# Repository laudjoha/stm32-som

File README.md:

# stm32-som
An application ready, hand solderable, stm32 system on module.

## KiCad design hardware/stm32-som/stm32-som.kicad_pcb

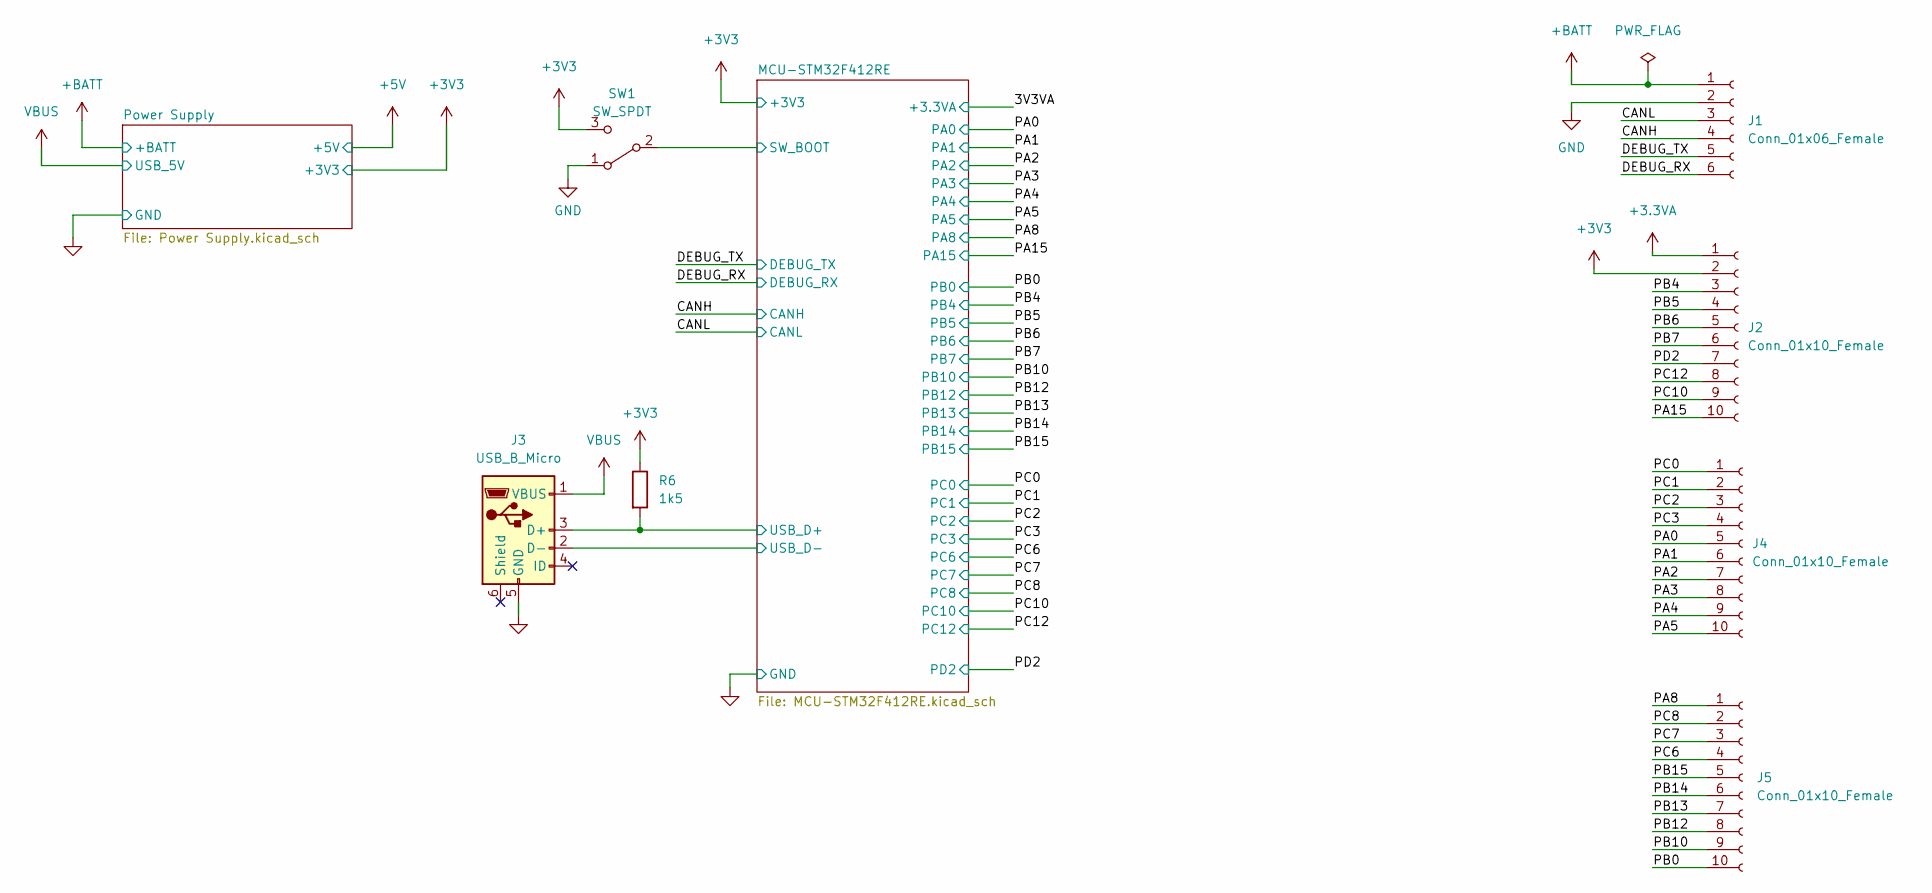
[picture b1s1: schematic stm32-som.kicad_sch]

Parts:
J1: Conn_01x06_Female; 1x6p-2.54mm-castellated
J2, J4, J5: Conn_01x10_Female; 1x10p-2.54mm-castellated
J3: USB_B_Micro; USB_Micro-B_Amphenol_10118194_Horizontal; JLC C132563
R6: 1k5; R_0402_1005Metric
SW1: SW_SPDT; SW_SPDT_PCM12

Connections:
+3.3VA: J2.1; also elsewhere on the board
+3V3: J2.2, R6.1, SW1.3 (C); also elsewhere on the board
+BATT: J1.1; also elsewhere on the board
/CANH: J1.4; also elsewhere on the board
/CANL: J1.3; also elsewhere on the board
/DEBUG_RX: J1.6; also elsewhere on the board
/DEBUG_TX: J1.5; also elsewhere on the board
/MCU-STM32F412RE/SW_BOOT: SW1.2 (B); also elsewhere on the board
/MCU-STM32F412RE/USB_D+: J3.3 (D+), R6.2; also elsewhere on the board
/MCU-STM32F412RE/USB_D-: J3.2 (D-); also elsewhere on the board
/PA0: J4.5; also elsewhere on the board
/PA1: J4.6; also elsewhere on the board
/PA2: J4.7; also elsewhere on the board
/PA3: J4.8; also elsewhere on the board
/PA4: J4.9; also elsewhere on the board
/PA5: J4.10; also elsewhere on the board
/PA8: J5.1; also elsewhere on the board
/PA15: J2.10; also elsewhere on the board
/PB0: J5.10; also elsewhere on the board
/PB4: J2.3; also elsewhere on the board
/PB5: J2.4; also elsewhere on the board
/PB6: J2.5; also elsewhere on the board
/PB7: J2.6; also elsewhere on the board
/PB10: J5.9; also elsewhere on the board
/PB12: J5.8; also elsewhere on the board
/PB13: J5.7; also elsewhere on the board
/PB14: J5.6; also elsewhere on the board
/PB15: J5.5; also elsewhere on the board
/PC0: J4.1; also elsewhere on the board
/PC1: J4.2; also elsewhere on the board
/PC2: J4.3; also elsewhere on the board
/PC3: J4.4; also elsewhere on the board
/PC6: J5.4; also elsewhere on the board
/PC7: J5.3; also elsewhere on the board
/PC8: J5.2; also elsewhere on the board
/PC10: J2.9; also elsewhere on the board
/PC12: J2.8; also elsewhere on the board
/PD2: J2.7; also elsewhere on the board
GND: J1.2, J3.5 (GND), SW1.1 (A); also elsewhere on the board
VBUS: J3.1 (VBUS); also elsewhere on the board

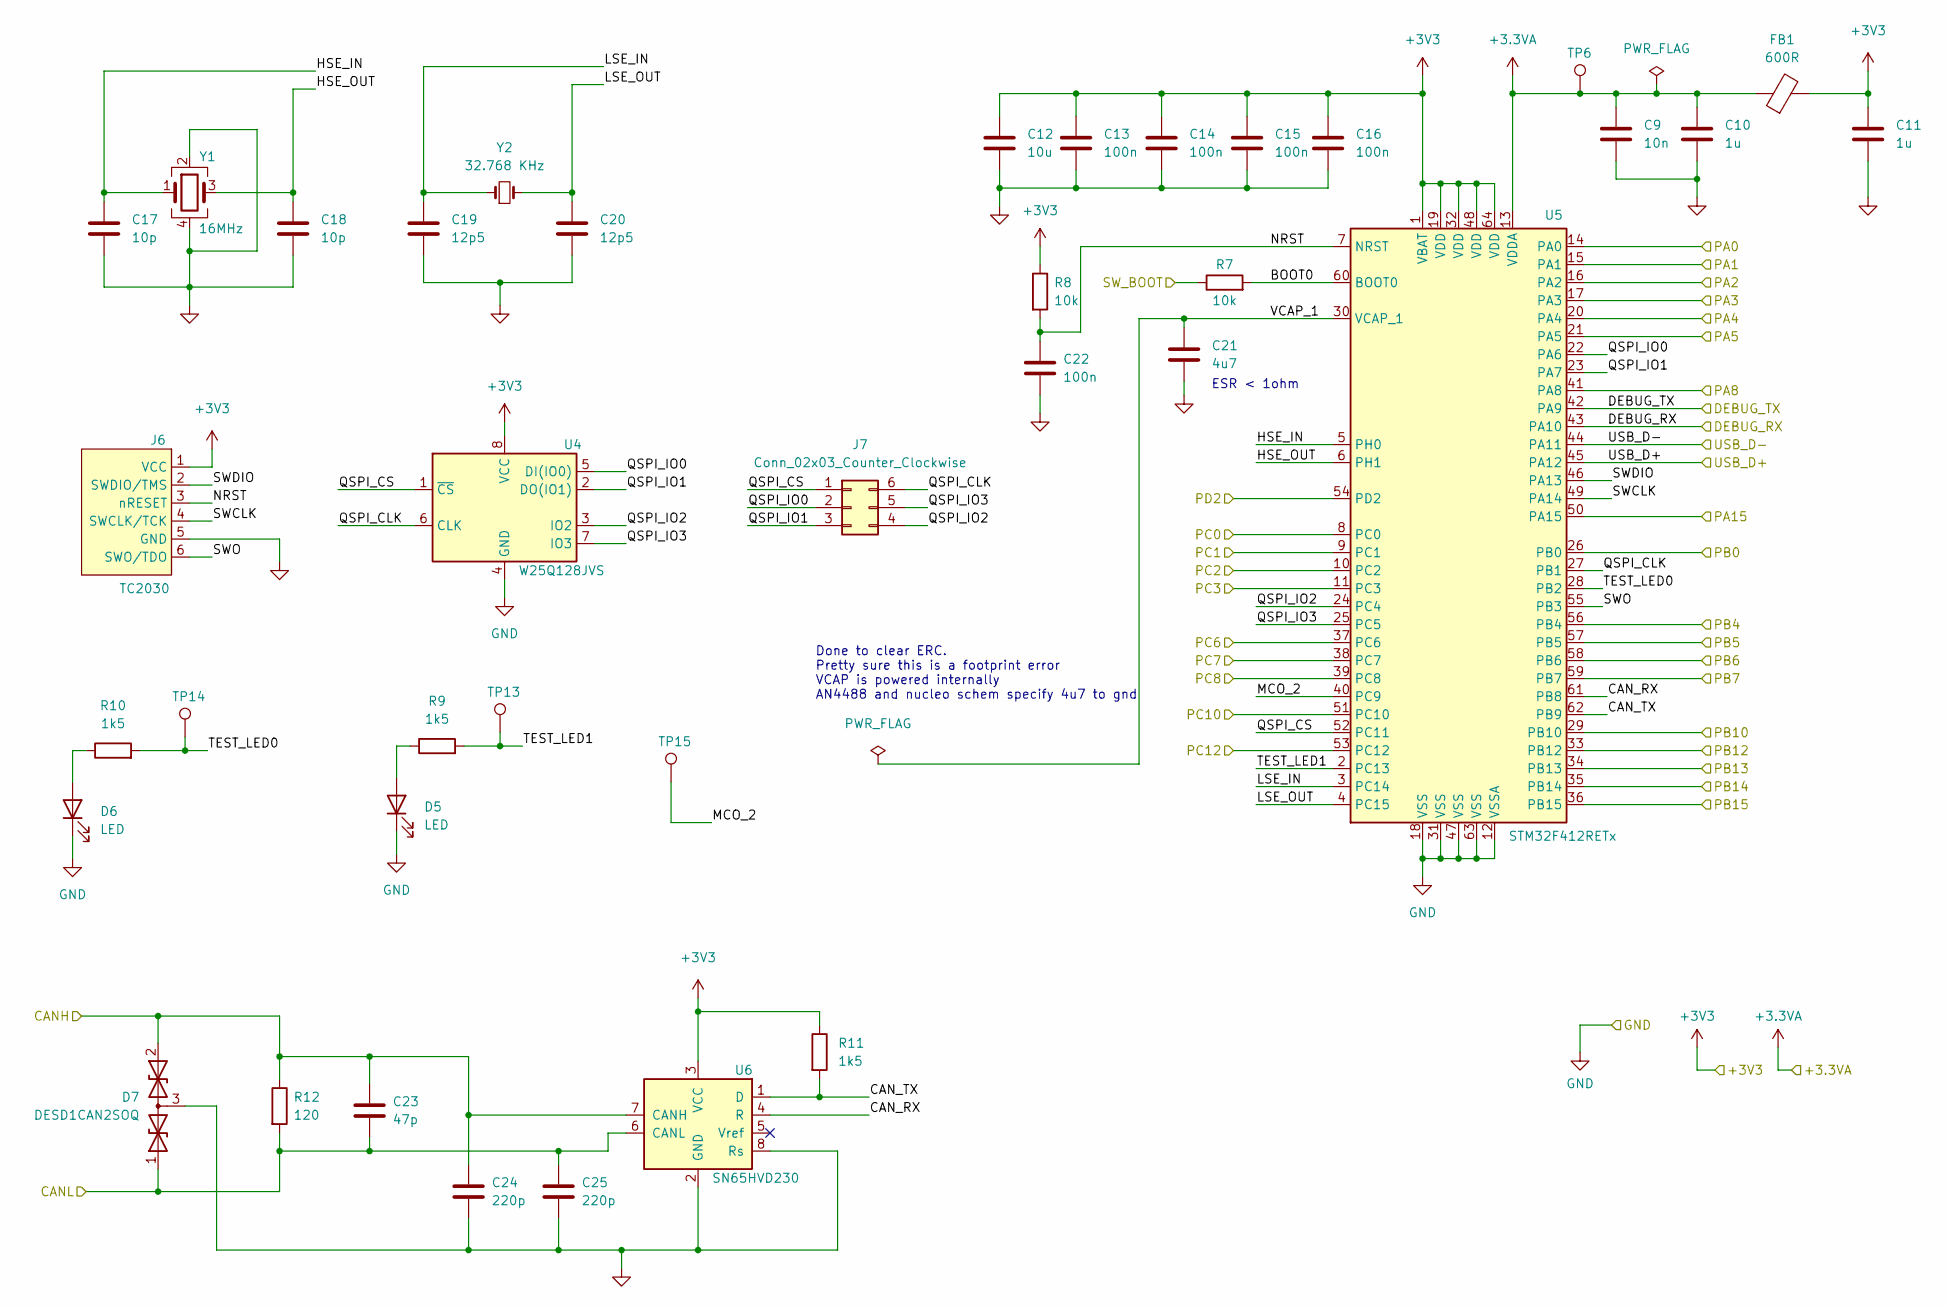
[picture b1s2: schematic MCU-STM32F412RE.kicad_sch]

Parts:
C9: 10n; C_0402_1005Metric
C10, C11: 1u; C_0603_1608Metric
C12: 10u; C_0805_2012Metric
C13, C14, C15, C16, C22: 100n; C_0402_1005Metric
C17, C18: 10p; C_0402_1005Metric
C19, C20: 12p5; C_0402_1005Metric
C21: 4u7; C_0603_1608Metric
C23: 47p; C_0402_1005Metric
C24, C25: 220p; C_0402_1005Metric
D5, D6: LED; LED_0603_1608Metric; JLC C2286
D7: DESD1CAN2SOQ; SOT-23; JLC C508188
FB1: 600R; L_0603_1608Metric; JLC C1002
J6: TC2030; Tag-Connect_TC2030-IDC-FP_2x03_P1.27mm_Vertical
J7: Conn_02x03_Counter_Clockwise; PinHeader_2x03_P1.27mm_Vertical_SMD; JLC C3975186
R7, R8: 10k; R_0402_1005Metric
R9, R10, R11: 1k5; R_0402_1005Metric
R12: 120; R_1206_3216Metric
TP6, TP13, TP14, TP15: TestPoint; TestPoint_Loop_D2.54mm_Drill1.5mm_Beaded
U4: W25Q128JVS; SOIC-8_5.23x5.23mm_P1.27mm
U5: STM32F412RETx; LQFP-64_10x10mm_P0.5mm
U6: SN65HVD230; SOIC-8_3.9x4.9mm_P1.27mm
Y1: 16MHz; Crystal_SMD_3225-4Pin_3.2x2.5mm; JLC C112972
Y2: 32.768 KHz; Crystal_SMD_3215-2Pin_3.2x1.5mm; JLC C32346

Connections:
+3.3VA: C9.1, C10.1, FB1.1, TP6.1, U5.13 (VDDA); also elsewhere on the board
+3V3: C11.1, C12.1, C13.1, C14.1, C15.1, C16.1, FB1.2, J6.1 (VCC), R8.1, R11.1, U4.8 (VCC), U5.1 (VBAT), U5.19 (VDD), U5.32 (VDD), U5.48 (VDD), U5.64 (VDD), U6.3 (VCC); also elsewhere on the board
/CANH: C23.1, C24.1, D7.2 (A2), R12.1, U6.7 (CANH); also elsewhere on the board
/CANL: C23.2, C25.1, D7.1 (A1), R12.2, U6.6 (CANL); also elsewhere on the board
/DEBUG_RX: U5.43 (PA10); also elsewhere on the board
/DEBUG_TX: U5.42 (PA9); also elsewhere on the board
/MCU-STM32F412RE/BOOT0: R7.2, U5.60 (BOOT0)
/MCU-STM32F412RE/CAN_RX: U5.61 (PB8), U6.4 (R)
/MCU-STM32F412RE/CAN_TX: R11.2, U5.62 (PB9), U6.1 (D)
/MCU-STM32F412RE/HSE_IN: C17.1, U5.5 (PH0), Y1.1
/MCU-STM32F412RE/HSE_OUT: C18.1, U5.6 (PH1), Y1.3
/MCU-STM32F412RE/LSE_IN: C19.1, U5.3 (PC14), Y2.1
/MCU-STM32F412RE/LSE_OUT: C20.1, U5.4 (PC15), Y2.2
/MCU-STM32F412RE/MCO_2: TP15.1, U5.40 (PC9)
/MCU-STM32F412RE/NRST: C22.1, J6.3 (nRESET), R8.2, U5.7 (NRST)
/MCU-STM32F412RE/QSPI_CLK: J7.6, U4.6 (CLK), U5.27 (PB1)
/MCU-STM32F412RE/QSPI_CS: J7.1, U4.1 (~CS), U5.52 (PC11)
/MCU-STM32F412RE/QSPI_IO0: J7.2, U4.5 (DI(IO0)), U5.22 (PA6)
/MCU-STM32F412RE/QSPI_IO1: J7.3, U4.2 (DO(IO1)), U5.23 (PA7)
/MCU-STM32F412RE/QSPI_IO2: J7.4, U4.3 (IO2), U5.24 (PC4)
/MCU-STM32F412RE/QSPI_IO3: J7.5, U4.7 (IO3), U5.25 (PC5)
/MCU-STM32F412RE/SWCLK: J6.4 (SWCLK/TCK), U5.49 (PA14)
/MCU-STM32F412RE/SWDIO: J6.2 (SWDIO/TMS), U5.46 (PA13)
/MCU-STM32F412RE/SWO: J6.6 (SWO/TDO), U5.55 (PB3)
/MCU-STM32F412RE/SW_BOOT: R7.1; also elsewhere on the board
/MCU-STM32F412RE/TEST_LED0: R10.2, TP14.1, U5.28 (PB2)
/MCU-STM32F412RE/TEST_LED1: R9.2, TP13.1, U5.2 (PC13)
/MCU-STM32F412RE/USB_D+: U5.45 (PA12); also elsewhere on the board
/MCU-STM32F412RE/USB_D-: U5.44 (PA11); also elsewhere on the board
/MCU-STM32F412RE/VCAP_1: C21.1, U5.30 (VCAP_1)
/PA0: U5.14 (PA0); also elsewhere on the board
/PA1: U5.15 (PA1); also elsewhere on the board
/PA2: U5.16 (PA2); also elsewhere on the board
/PA3: U5.17 (PA3); also elsewhere on the board
/PA4: U5.20 (PA4); also elsewhere on the board
/PA5: U5.21 (PA5); also elsewhere on the board
/PA8: U5.41 (PA8); also elsewhere on the board
/PA15: U5.50 (PA15); also elsewhere on the board
/PB0: U5.26 (PB0); also elsewhere on the board
/PB4: U5.56 (PB4); also elsewhere on the board
/PB5: U5.57 (PB5); also elsewhere on the board
/PB6: U5.58 (PB6); also elsewhere on the board
/PB7: U5.59 (PB7); also elsewhere on the board
/PB10: U5.29 (PB10); also elsewhere on the board
/PB12: U5.33 (PB12); also elsewhere on the board
/PB13: U5.34 (PB13); also elsewhere on the board
/PB14: U5.35 (PB14); also elsewhere on the board
/PB15: U5.36 (PB15); also elsewhere on the board
/PC0: U5.8 (PC0); also elsewhere on the board
/PC1: U5.9 (PC1); also elsewhere on the board
/PC2: U5.10 (PC2); also elsewhere on the board
/PC3: U5.11 (PC3); also elsewhere on the board
/PC6: U5.37 (PC6); also elsewhere on the board
/PC7: U5.38 (PC7); also elsewhere on the board
/PC8: U5.39 (PC8); also elsewhere on the board
/PC10: U5.51 (PC10); also elsewhere on the board
/PC12: U5.53 (PC12); also elsewhere on the board
/PD2: U5.54 (PD2); also elsewhere on the board
GND: C9.2, C10.2, C11.2, C12.2, C13.2, C14.2, C15.2, C16.2, C17.2, C18.2, C19.2, C20.2, C21.2, C22.2, C24.2, C25.2, D5.1 (K), D6.1 (K), D7.3 (common), J6.5 (GND), U4.4 (GND), U5.12 (VSSA), U5.18 (VSS), U5.31 (VSS), U5.47 (VSS), U5.63 (VSS), U6.2 (GND), U6.8 (Rs), Y1.2, Y1.4; also elsewhere on the board
unnamed: D5.2 (A), R9.1
unnamed: D6.2 (A), R10.1

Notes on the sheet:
Done to clear ERC. Pretty sure this is a footprint error VCAP is powered internally AN4488 and nucleo schem specify 4u7 to gnd
ESR < 1ohm

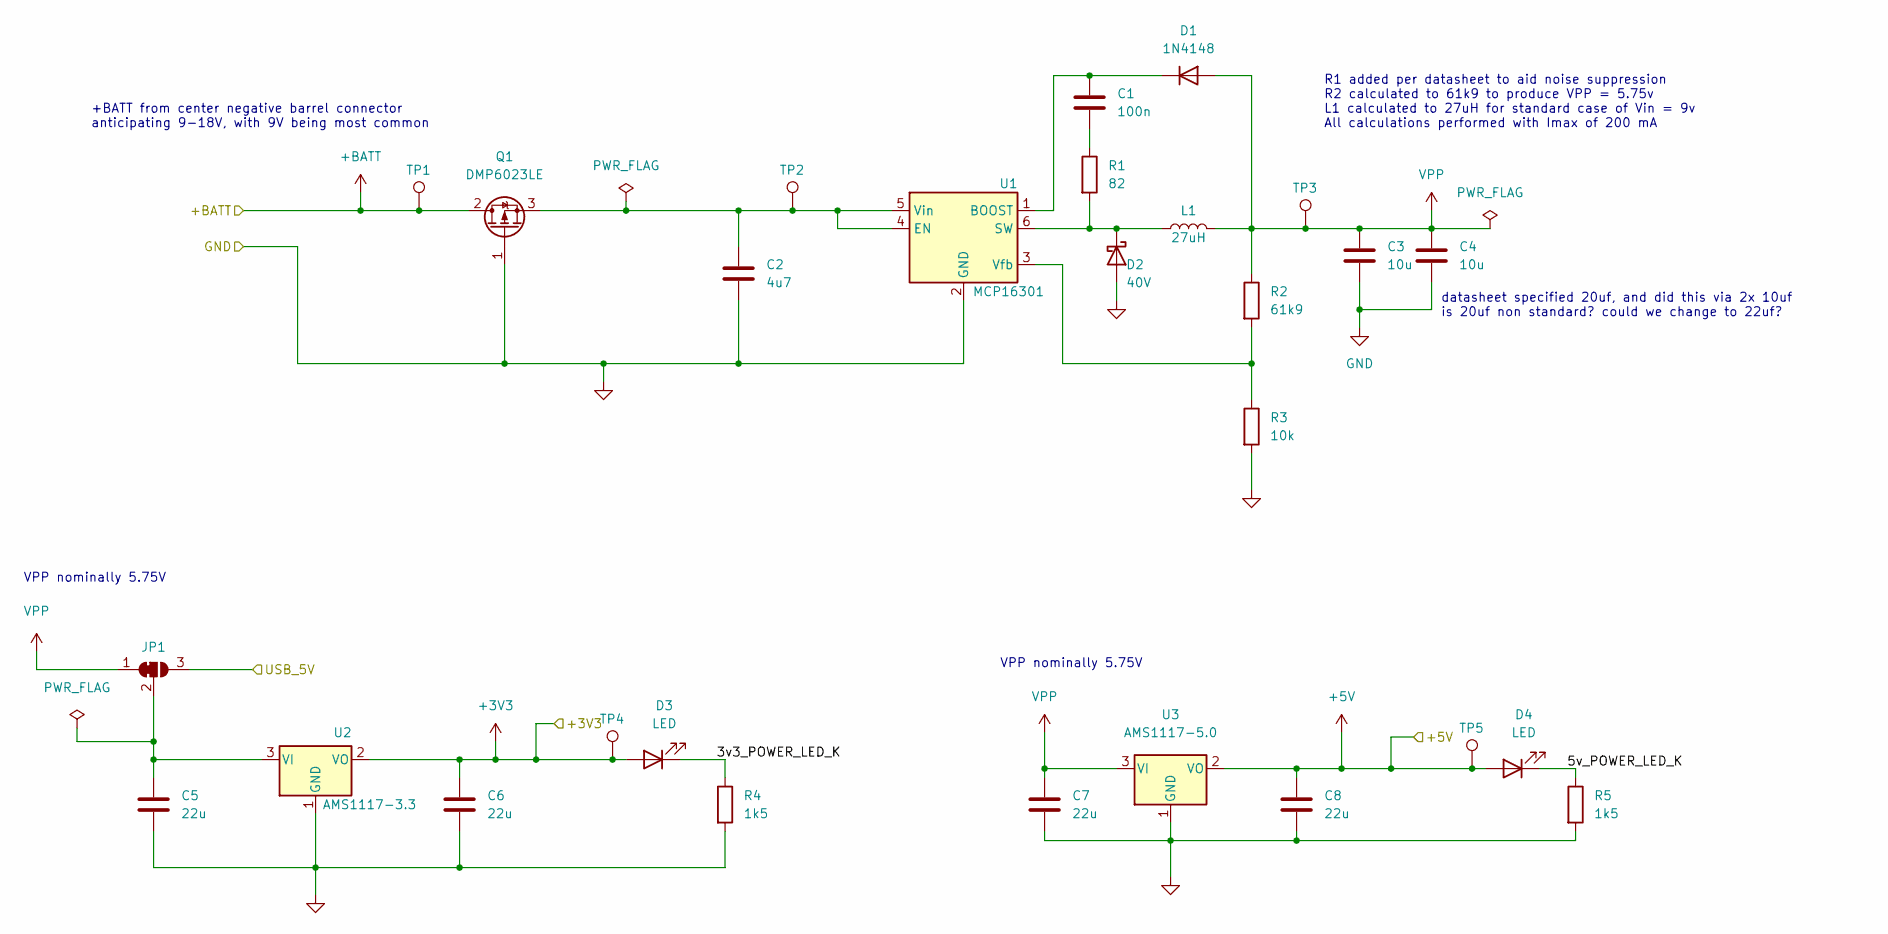
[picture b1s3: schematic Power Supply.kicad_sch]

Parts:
C1: 100n; C_0402_1005Metric
C2: 4u7; C_0805_2012Metric
C3, C4: 10u; C_0805_2012Metric
C5, C6, C7, C8: 22u; C_0805_2012Metric
D1: 1N4148; D_SOD-123; JLC C727110
D2: 40V; D_SOD-123; JLC C8598
D3, D4: LED; LED_0603_1608Metric; JLC C2286
JP1: SolderJumper_3_Bridged12; SolderJumper-3_P1.3mm_Bridged12_Pad1.0x1.5mm_NumberLabels
L1: 27uH; L_1812_4532Metric; JLC C394126
Q1: DMP6023LE; SOT-223-3_TabPin2; JLC C154901
R1: 82; R_0603_1608Metric
R2: 61k9; R_0805_2012Metric
R3: 10k; R_0805_2012Metric
R4, R5: 1k5; R_0402_1005Metric
TP1, TP2, TP3, TP4, TP5: TestPoint; TestPoint_Loop_D2.54mm_Drill1.5mm_Beaded
U1: MCP16301; SOT-23-6
U2: AMS1117-3.3; SOT-223-3_TabPin2
U3: AMS1117-5.0; SOT-223-3_TabPin2

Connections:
+3V3: C6.1, D3.2 (A), TP4.1, U2.2 (VO); also elsewhere on the board
+5V: C8.1, D4.2 (A), TP5.1, U3.2 (VO)
+BATT: Q1.2 (D), TP1.1; also elsewhere on the board
/Power Supply/3v3_POWER_LED_K: D3.1 (K), R4.1
/Power Supply/5v_POWER_LED_K: D4.1 (K), R5.1
GND: C2.2, C3.2, C4.2, C5.2, C6.2, C7.2, C8.2, D2.2 (A), Q1.1 (G), R3.2, R4.2, R5.2, U1.2 (GND), U2.1 (GND), U3.1 (GND); also elsewhere on the board
unnamed: C1.1, D1.1 (K), U1.1 (BOOST)
unnamed: C1.2, R1.1
unnamed: C2.1, Q1.3 (S), TP2.1, U1.4 (EN), U1.5 (Vin)
unnamed: C5.1, JP1.2 (C), U2.3 (VI)
unnamed: D2.1 (K), L1.1, R1.2, U1.6 (SW)
unnamed: R2.2, R3.1, U1.3 (Vfb)
VBUS: JP1.3 (B); also elsewhere on the board
VPP: C3.1, C4.1, C7.1, D1.2 (A), JP1.1 (A), L1.2, R2.1, TP3.1, U3.3 (VI)

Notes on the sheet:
VPP nominally 5.75V
R1 added per datasheet to aid noise suppression R2 calculated to 61k9 to produce VPP = 5.75v L1 calculated to 27uH for standard case of Vin = 9v All calculations performed with Imax of 200 mA
datasheet specified 20uf, and did this via 2x 10uf is 20uf non standard? could we change to 22uf?
+BATT from center negative barrel connector anticipating 9-18V, with 9V being most common

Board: 2 copper layers, 73 parts (0 on the bottom side), 73 nets, no tracks yet.

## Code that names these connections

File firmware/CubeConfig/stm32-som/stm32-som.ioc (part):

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Mcu.Name=STM32F412R(E-G)Tx
Mcu.Package=LQFP64
Mcu.UserName=STM32F412RETx
PA10.Mode=Asynchronous
PA10.Signal=USART1_RX
PA11.Mode=Device_Only
PA11.Signal=USB_OTG_FS_DM
PA12.Mode=Device_Only
PA12.Signal=USB_OTG_FS_DP
PA13.Mode=Trace_Asynchronous_SW
PA13.Signal=SYS_JTMS-SWDIO
PA14.Mode=Trace_Asynchronous_SW
PA14.Signal=SYS_JTCK-SWCLK
PA6.Mode=Single Bank 2
PA6.Signal=QUADSPI_BK2_IO0
PA7.Mode=Single Bank 2
PA7.Signal=QUADSPI_BK2_IO1
PA9.Mode=Asynchronous
PA9.Signal=USART1_TX
PB1.Mode=Single Bank 2
PB1.Signal=QUADSPI_CLK
PB2.GPIOParameters=GPIO_Label
PB2.GPIO_Label=TEST_LED0
PB2.Signal=GPIO_Output
PB3.Mode=Trace_Asynchronous_SW
PB3.Signal=SYS_JTDO-SWO
PB8.Mode=Master
PB8.Signal=CAN1_RX
PB9.Mode=Master
PB9.Signal=CAN1_TX
PC11.Mode=Single Bank 2
PC11.Signal=QUADSPI_BK2_NCS
PC13.GPIOParameters=GPIO_Label
PC13.GPIO_Label=TEST_LED1
PC13.Signal=GPIO_Output
PC14-OSC32_IN.Mode=LSE-External-Oscillator
PC14-OSC32_IN.Signal=RCC_OSC32_IN
PC15-OSC32_OUT.Mode=LSE-External-Oscillator
PC15-OSC32_OUT.Signal=RCC_OSC32_OUT
PC4.Mode=Single Bank 2
PC4.Signal=QUADSPI_BK2_IO2
PC5.Mode=Single Bank 2
PC5.Signal=QUADSPI_BK2_IO3
PC9.Mode=Clock-out-2
PC9.Signal=RCC_MCO_2
PH0\ -\ OSC_IN.Mode=HSE-External-Oscillator
PH0\ -\ OSC_IN.Signal=RCC_OSC_IN
PH1\ -\ OSC_OUT.Mode=HSE-External-Oscillator
PH1\ -\ OSC_OUT.Signal=RCC_OSC_OUT
RCC.HSE_VALUE=16000000
RCC.SYSCLKFreq_VALUE=96000000
RCC.SYSCLKSource=RCC_SYSCLKSOURCE_PLLCLK
board=custom

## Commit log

2023-04-28 file structure
2023-04-28 ignore kicad backups
2023-04-28 kicad project setup
2023-04-28 cubemx project setup
2023-04-29 ignore datasheets folder
2023-08-21 add kicad auto save files to git ignore
2023-08-21 add power supply to som, change MCU to STM32F412RE, draw MCU schematic layer
2023-08-21 update MCU to STM32F412RE in CubeMX
2023-08-27 add test points, complete top hierarchical level, correct jtag mcu connection
2023-08-27 clear ERC, small question about voltage level and rail timing on VCAP, but otherwise net name stuff
2023-08-27 add 1x6 and 1x10 castellated connectors to custom footprint library
2023-08-27 add footprints to all components, JLC part numbers to to everything except capacitors and resistors
2023-09-29 swap big qspi test points for small test header, complete rough layout
